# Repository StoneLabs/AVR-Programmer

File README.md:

# Stone Labs. AVR-Programmer
Schematics and firmware for a portable In-Service-Programmer. It is designed to be powered by a 9V battery and uses an OLED Display module for user interaction. INTEL HEX Files can be flashed to target chips via an ISP-6 port directly from an SD-Card.

# PCB

The Programmer is designed to sit on a portable ~9x11cm PCB. Eagle files for the PCB can be found in the `schematics` folder. Target chips can be programmed with the 6-pin Header located at the top of the PCB. There is also an 8Mhz clock pin available (TCLK) in case the target needs an external clock and none is available. BOM for the programmer can be found in `schematics/bom-grouped.csv`. All parts are available from DIGI-KEY. The price per assembled PCB should be around 10-30 bucks depending on the order quantity.

Aside from the programmer, there is target PCB design under `schematics-target`. The target can hold an ATmega328P like chip that can be programmed by connecting the target boards ISP Header to the programmer ISP-Port.

[Picture of PCB revision 1 (Release_V-1.0)](/pcb_v-1.0.png)

| PCB | Version | Status |
| - | - | - |
| Main PCB | Hardware_V-1.0 | Pull-Ups R1, R2 are connected incorrectly (to GND instead of +5V)! Assembled and tested. Works without R1, R2. |
| Main PCB | Hardware_V-1.1 | Fixed only R1, R2 and should work better than V-1.0. Untested! |
| Main PCB | Hardware_V-1.1+ | No functional hardware change. |
| Target PCB | Hardware_V-1.2 | Assembled and tested. Fully functional. |

# INTEL HEX

All `.hex` or `.HEX` files in the root folder of the SD-Card can be flashed to the target using the Programmer. The algorithm used for flashing the program to the target is very robust against weirdly formed hex files (e.g. line swaps, different lengths of lines in the same file, etc.). HEX record types 00, 01, and 02 are fully supported. Type 03 entries will be ignored with a warning sent to the programmers Serial output. Type 04 and 05 are not supported and HEX files containing those record types can't be flashed. (This shouldn't be an issue for AVR chips).

The programmer will also scan all possible bootloader positions for the current target and automatically set the fuse containing the bootloader position bits as needed.

# Supported chips

 Supported and tested  
 Supported not tested  
 Not yet supported  

||Chip||Chip|
| - | - | - | - |
|   | ATmega1280    |   | ATmega329A    |
|   | ATmega1281    |   | ATmega329PA   |
|   | ATmega1284P   |   | ATmega329P    |
|   | ATmega1284    |   | ATmega329     |
|   | ATmega128A    |   | ATmega32A     |
|   | ATmega128RFA1 |   | ATmega32C1    |
|   | ATmega128     |   | ATmega32HVB   |
|   | ATmega162     |   | ATmega32M1    |
|   | ATmega164A    |   | ATmega32U2    |
|   | ATmega164PA   |   | ATmega32U4    |
|   | ATmega164P    |   | ATmega32      |
|   | ATmega165A    |   | ATmega48A     |
|   | ATmega165PA   |   | ATmega48PA    |
|   | ATmega165P    |   | ATmega48P     |
|   | ATmega168A    |   | ATmega48      |
|   | ATmega168PA   |   | ATmega640     |
|   | ATmega168P    |   | ATmega644A    |
|   | ATmega168V    |   | ATmega644PA   |
|   | ATmega168     |   | ATmega644P    |
|   | ATmega169A    |   | ATmega644     |
|   | ATmega169PA   |   | ATmega6450A   |
|   | ATmega169P    |   | ATmega6450P   |
|   | ATmega16A     |   | ATmega6450    |
|   | ATmega16HVB   |   | ATmega645A    |
|   | ATmega16M1    |   | ATmega645P    |
|   | ATmega16U2    |   | ATmega645     |
|   | ATmega16U4    |   | ATmega6490A   |
|   | ATmega16      |   | ATmega6490P   |
|   | ATmega2560    |   | ATmega6490    |
|   | ATmega2561    |   | ATmega649A    |
|   | ATmega324A    |   | ATmega649P    |
|   | ATmega324PA   |   | ATmega649     |
|   | ATmega324P    |   | ATmega64A     |
|   | ATmega3250A   |   | ATmega64C1    |
|   | ATmega3250PA  |   | ATmega64M1    |
|   | ATmega3250P   |   | ATmega64      |
|   | ATmega3250    |   | ATmega8515    |
|   | ATmega325A    |   | ATmega8535    |
|   | ATmega325PA   |   | ATmega88A     |
|   | ATmega325P    |   | ATmega88PA    |
|   | ATmega325     |   | ATmega88P     |
|   | ATmega328P    |   | ATmega88      |
|   | ATmega328PB   |   | ATmega8A      |
|   | ATmega328     |   | ATmega8U2     |
|   | ATmega3290A   |   | ATmega8       |
|   | ATmega3290PA  |   | At90USB82     |
|   | ATmega3290P   |   | At90USB162    |
|   | ATmega3290    |                                                                  |               |
| | | | |
|   | ATtiny24      |   | ATtiny25      |
|   | ATtiny44      |   | ATtiny45      |
|   | ATtiny84      |   | ATtiny85      |

# License

This is free and unencumbered software released into the public domain.

Anyone is free to copy, modify, publish, use, compile, sell, or
distribute this software, either in source code form or as a compiled
binary, for any purpose, commercial or non-commercial, and by any
means.

In jurisdictions that recognize copyright laws, the author or authors
of this software dedicate any and all copyright interest in the
software to the public domain. We make this dedication for the benefit
of the public at large and to the detriment of our heirs and
successors. We intend this dedication to be an overt act of
relinquishment in perpetuity of all present and future rights to this
software under copyright law.

THE SOFTWARE IS PROVIDED "AS IS", WITHOUT WARRANTY OF ANY KIND,
EXPRESS OR IMPLIED, INCLUDING BUT NOT LIMITED TO THE WARRANTIES OF
MERCHANTABILITY, FITNESS FOR A PARTICULAR PURPOSE AND NONINFRINGEMENT.
IN NO EVENT SHALL THE AUTHORS BE LIABLE FOR ANY CLAIM, DAMAGES OR
OTHER LIABILITY, WHETHER IN AN ACTION OF CONTRACT, TORT OR OTHERWISE,
ARISING FROM, OUT OF OR IN CONNECTION WITH THE SOFTWARE OR THE USE OR
OTHER DEALINGS IN THE SOFTWARE.

For more information, please refer to <http://unlicense.org/>

### That being said, I'd really like to hear from you if you plan on using this project somewhere. And I for sure wouldn't mind some part if you use it commercially ;) (e.g. selling it etc.)

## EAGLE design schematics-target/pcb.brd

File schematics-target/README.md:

# Schematics

Eagle files for a simple target board holding an ATmega328P like chip in PDIP packaging. It can be used to easily hook up target chips.

The Graphics on the pcb can be found in media/.

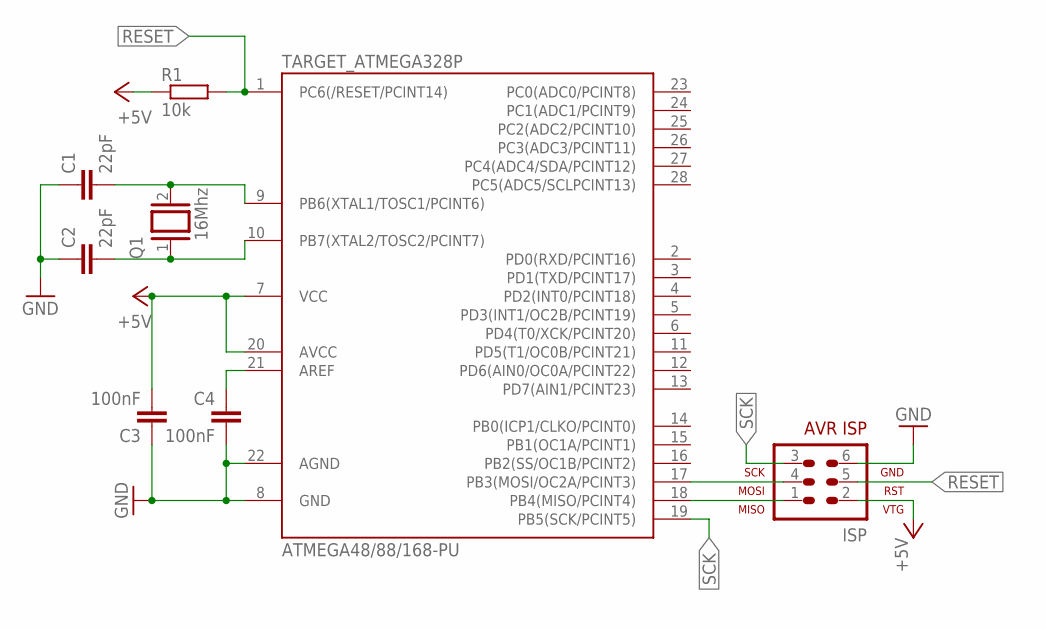
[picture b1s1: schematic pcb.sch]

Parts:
C1, C2: 22pF; C0805
C3, C4: 100nF; C0805
ISP: AVR-ISP-6
Q1: 16Mhz; QS
R1: 10k; R0805
TARGET_ATMEGA328P: ATMEGA48/88/168-PU; DIL28-3

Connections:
+5V: C3.2, ISP.2, R1.1, TARGET_ATMEGA328P.7 (VCC), TARGET_ATMEGA328P.20 (AVCC)
GND: C1.1, C2.1, C3.1, C4.2, ISP.6, TARGET_ATMEGA328P.8 (GND), TARGET_ATMEGA328P.22 (AGND)
unnamed: ISP.4, TARGET_ATMEGA328P.17 (PB3(MOSI/OC2A/PCINT3))
unnamed: ISP.1, TARGET_ATMEGA328P.18 (PB4(MISO/PCINT4))
unnamed: C1.2, Q1.2, TARGET_ATMEGA328P.9 (PB6(XTAL1/TOSC1/PCINT6))
unnamed: C2.2, Q1.1, TARGET_ATMEGA328P.10 (PB7(XTAL2/TOSC2/PCINT7))
unnamed: C4.1, TARGET_ATMEGA328P.21 (AREF)
RESET: ISP.5, R1.2, TARGET_ATMEGA328P.1 (PC6(/RESET/PCINT14))
SCK: ISP.3, TARGET_ATMEGA328P.19 (PB5(SCK/PCINT5))

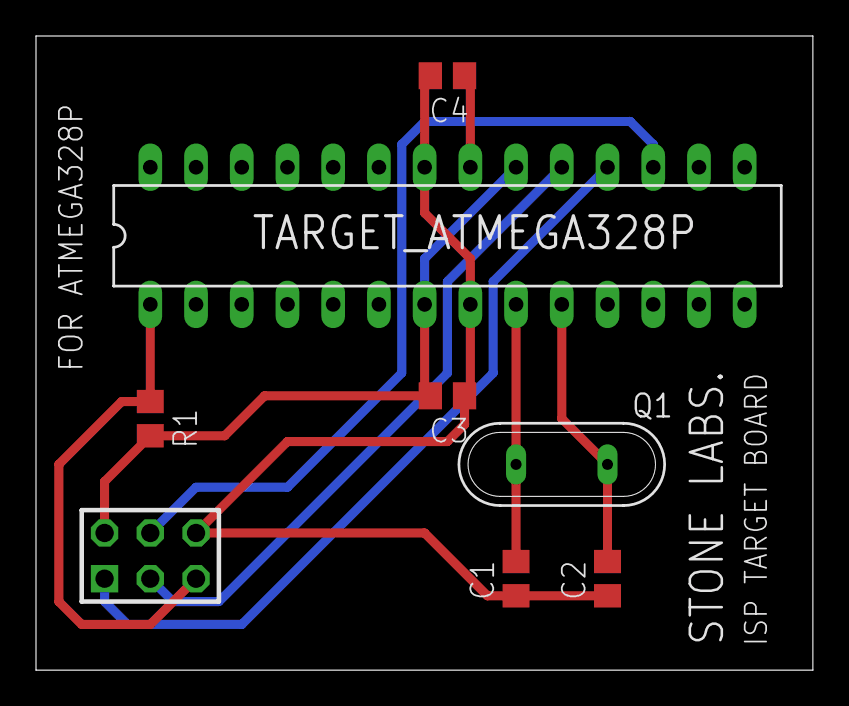
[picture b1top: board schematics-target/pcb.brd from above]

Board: 2 copper layers, 43.2 x 35.2 mm, 8 parts (0 on the bottom side), 9 nets.

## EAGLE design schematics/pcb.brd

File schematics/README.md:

# Schematics

Eagle files for the programmer board as well as a diagram for arduino based testing (arduino_wiring.sch).

Parts.lbr contains the OLED screen used. (see also oled.jpg)

The Graphics on the pcb can be found in media/.

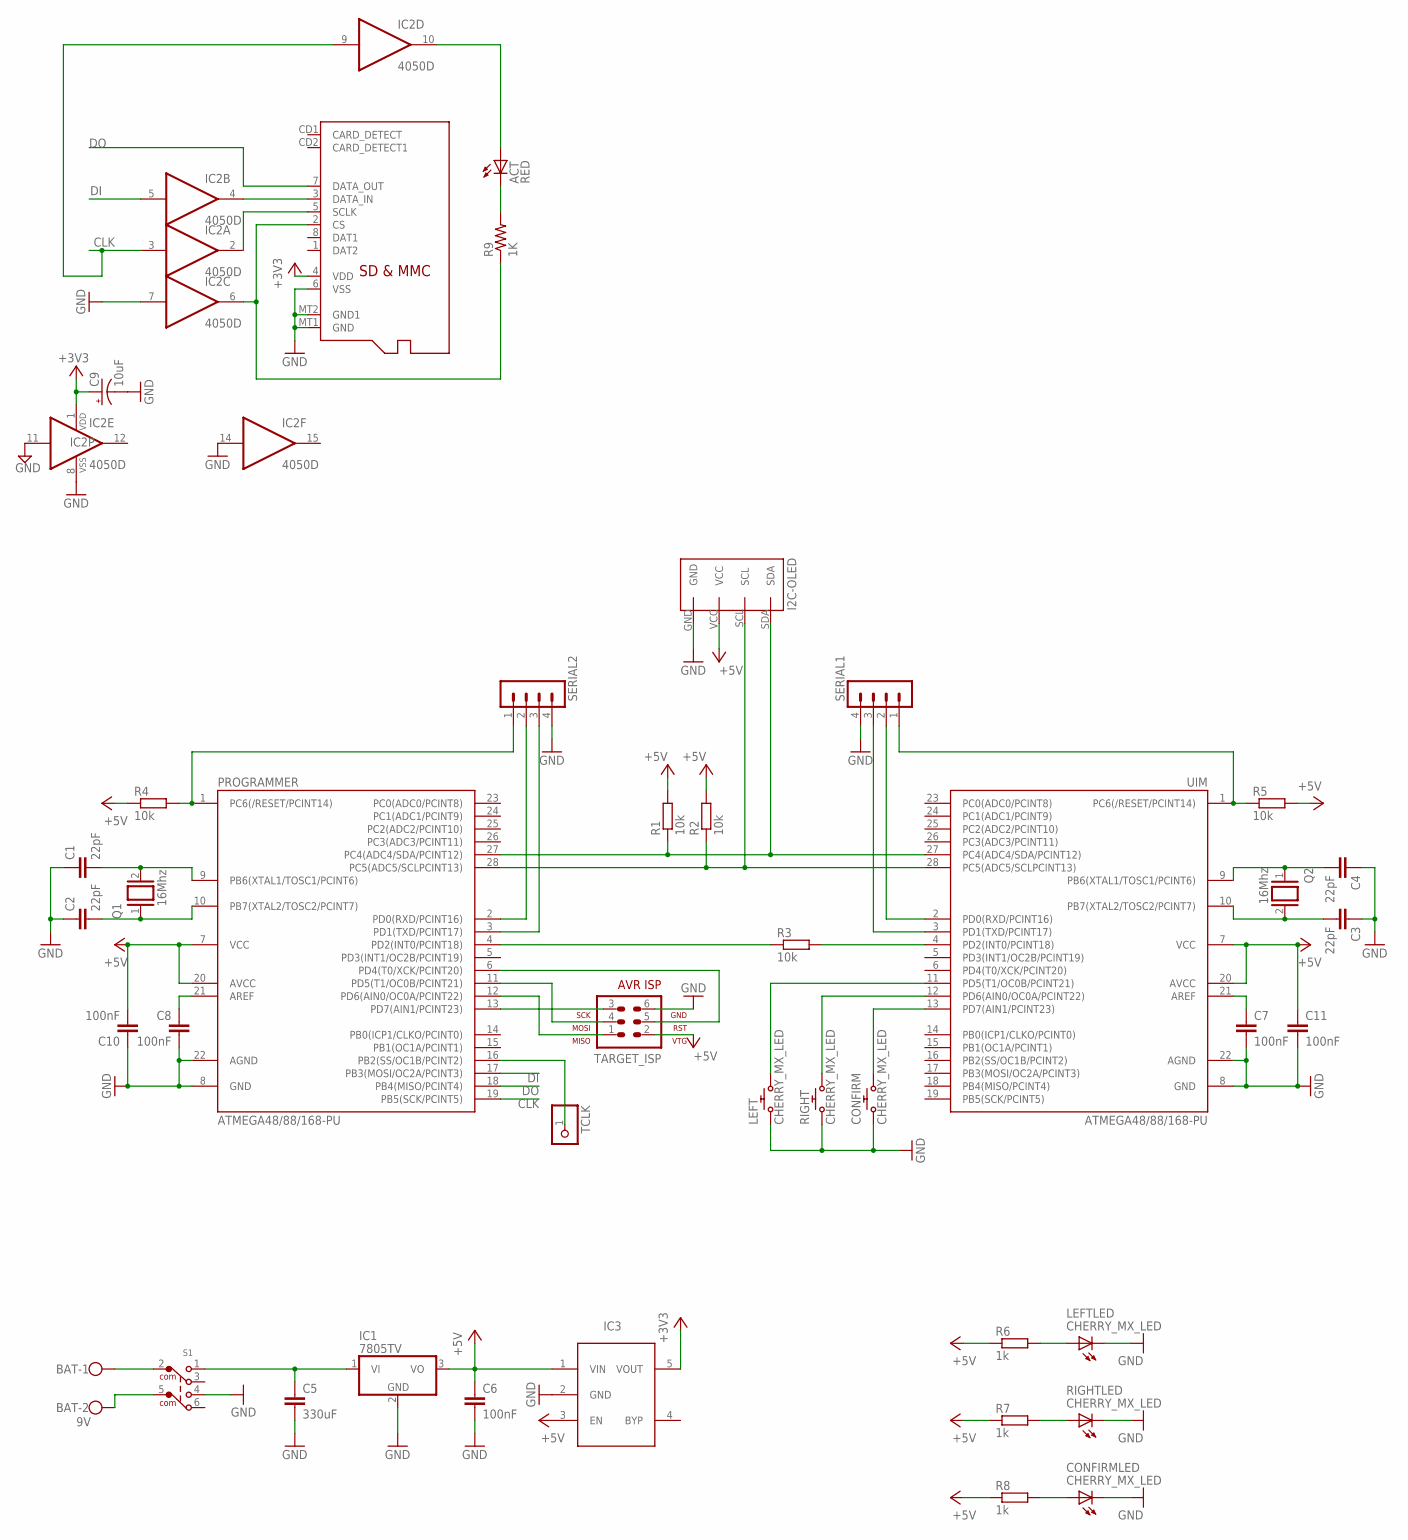
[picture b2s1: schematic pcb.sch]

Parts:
ACT: RED; CHIP-LED0805
BAT: 9V; W237-102
C1, C2, C3, C4: 22pF; C0805
C5: 330uF; C0805
C6, C7, C8, C10, C11: 100nF; C0805
C9: 10uF; A/3216-18R
CONFIRM: CHERRY_MX_LED
IC1: 7805TV; TO220V
IC2: 4050D; SO16
IC3: LP298XS; SOT23-5L
LEFT: CHERRY_MX_LED
PROGRAMMER: ATMEGA48/88/168-PU; DIL28-3
Q1, Q2: 16Mhz; QS
R1, R2, R3, R4, R5: 10k; R0805
R6, R7, R8: 1k; R0805
R9: 1K; R0805
RIGHT: CHERRY_MX_LED
S1: 452404020202
SERIAL1, SERIAL2: MA04-1
TARGET_ISP: AVR-ISP-6
TCLK: PINHD-1X1; 1X01
U$1: 128X64-I2C-OLED
UIM: ATMEGA48/88/168-PU; DIL28-3
X1: MICROSD

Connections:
9V+: C5.1, IC1.1 (VI), S1.1
+3V3: C9.+, IC2.1 (VDD), IC3.5 (VOUT), X1.4 (VDD)
+5V: C6.1, C10.2, C11.1, IC1.3 (VO), IC3.1 (VIN), IC3.3 (EN), PROGRAMMER.7 (VCC), PROGRAMMER.20 (AVCC), R1.2, R2.2, R4.1, R5.2, R6.1, R7.1, R8.1, TARGET_ISP.2, U$1.VCC, UIM.7 (VCC), UIM.20 (AVCC)
B$1: PROGRAMMER.11 (PD5(T1/OC0B/PCINT21)), TARGET_ISP.4
BAT+: BAT.1, S1.2 (COM)
BAT-: BAT.2, S1.5 (COM1)
CLK: IC2.3 (I), IC2.9 (I), PROGRAMMER.19 (PB5(SCK/PCINT5))
DI: IC2.5 (I), PROGRAMMER.17 (PB3(MOSI/OC2A/PCINT3))
DO: PROGRAMMER.18 (PB4(MISO/PCINT4)), X1.7 (DATA_OUT)
GND: C1.1, C2.1, C3.1, C4.1, C5.2, C6.2, C7.2, C8.2, C9.-, C10.1, C11.2, CONFIRM.L2 (C), CONFIRM.S1 (1), IC1.2 (GND), IC2.7 (I), IC2.8 (VSS), IC2.11 (I), IC2.14 (I), IC3.2 (GND), LEFT.L2 (C), LEFT.S1 (1), PROGRAMMER.8 (GND), PROGRAMMER.22 (AGND), RIGHT.L2 (C), RIGHT.S1 (1), S1.4, SERIAL1.4, SERIAL2.4, TARGET_ISP.6, U$1.GND, UIM.8 (GND), UIM.22 (AGND), X1.6 (VSS), X1.MT1 (GND), X1.MT2 (GND1)
unnamed: PROGRAMMER.28 (PC5(ADC5/SCLPCINT13)), R2.1, U$1.SCL, UIM.28 (PC5(ADC5/SCLPCINT13))
unnamed: PROGRAMMER.27 (PC4(ADC4/SDA/PCINT12)), R1.1, U$1.SDA, UIM.27 (PC4(ADC4/SDA/PCINT12))
unnamed: PROGRAMMER.4 (PD2(INT0/PCINT18)), R3.1
unnamed: R3.2, UIM.4 (PD2(INT0/PCINT18))
unnamed: PROGRAMMER.1 (PC6(/RESET/PCINT14)), R4.2, SERIAL2.1
unnamed: R5.1, SERIAL1.1, UIM.1 (PC6(/RESET/PCINT14))
unnamed: C1.2, PROGRAMMER.9 (PB6(XTAL1/TOSC1/PCINT6)), Q1.2
unnamed: C2.2, PROGRAMMER.10 (PB7(XTAL2/TOSC2/PCINT7)), Q1.1
unnamed: LEFT.S2 (2), UIM.11 (PD5(T1/OC0B/PCINT21))
unnamed: C3.2, Q2.2, UIM.10 (PB7(XTAL2/TOSC2/PCINT7))
unnamed: C4.2, Q2.1, UIM.9 (PB6(XTAL1/TOSC1/PCINT6))
unnamed: PROGRAMMER.12 (PD6(AIN0/OC0A/PCINT22)), TARGET_ISP.1
unnamed: PROGRAMMER.13 (PD7(AIN1/PCINT23)), TARGET_ISP.3
unnamed: PROGRAMMER.6 (PD4(T0/XCK/PCINT20)), TARGET_ISP.5
unnamed: RIGHT.S2 (2), UIM.12 (PD6(AIN0/OC0A/PCINT22))
unnamed: CONFIRM.S2 (2), UIM.13 (PD7(AIN1/PCINT23))
unnamed: LEFT.L1 (A), R6.2
unnamed: R7.2, RIGHT.L1 (A)
unnamed: CONFIRM.L1 (A), R8.2
unnamed: C7.1, UIM.21 (AREF)
unnamed: C8.1, PROGRAMMER.21 (AREF)
unnamed: ACT.A, IC2.10 (O)
unnamed: IC2.2 (O), X1.5 (SCLK)
unnamed: IC2.6 (O), R9.1, X1.2 (CS)
unnamed: ACT.C, R9.2
unnamed: IC2.4 (O), X1.3 (DATA_IN)
unnamed: PROGRAMMER.16 (PB2(SS/OC1B/PCINT2)), TCLK.1
unnamed: PROGRAMMER.2 (PD0(RXD/PCINT16)), SERIAL2.2
unnamed: PROGRAMMER.3 (PD1(TXD/PCINT17)), SERIAL2.3
unnamed: SERIAL1.2, UIM.2 (PD0(RXD/PCINT16))
unnamed: SERIAL1.3, UIM.3 (PD1(TXD/PCINT17))

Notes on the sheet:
I2C-OLED

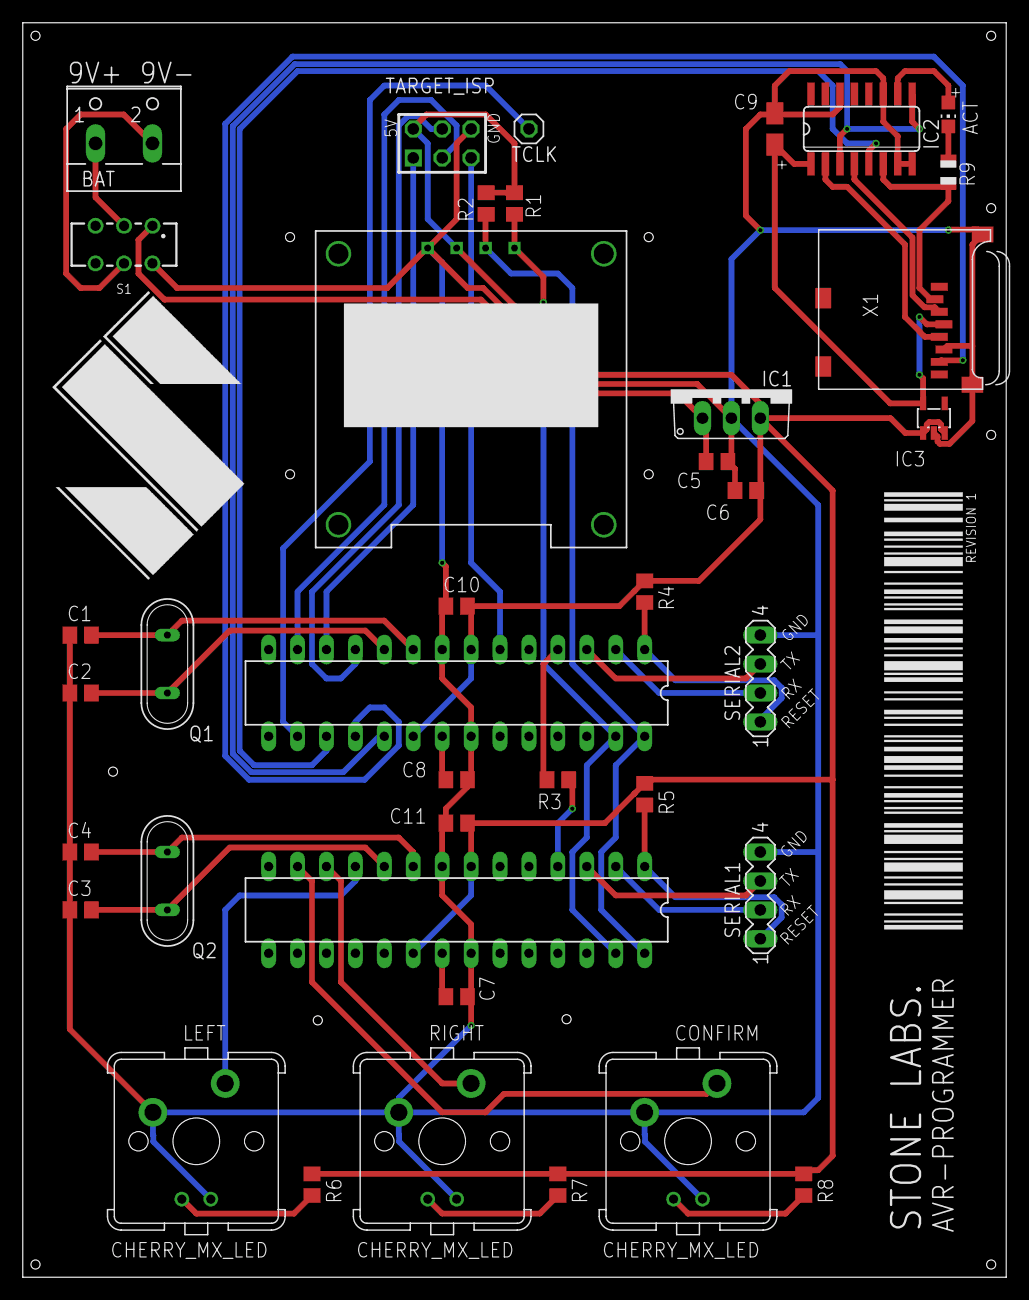
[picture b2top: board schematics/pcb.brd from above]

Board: 2 copper layers, 86.4 x 110.2 mm, 39 parts (0 on the bottom side), 41 nets.

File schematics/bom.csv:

Part,Value,Device,Package,Description
ACT,RED,LEDCHIP-LED0805,CHIP-LED0805,LED
BAT,9V,W237-102,W237-102,WAGO SCREW CLAMP
C1,22pF,C-EUC0805,C0805,"CAPACITOR, European symbol"
C2,22pF,C-EUC0805,C0805,"CAPACITOR, European symbol"
C3,22pF,C-EUC0805,C0805,"CAPACITOR, European symbol"
C4,22pF,C-EUC0805,C0805,"CAPACITOR, European symbol"
C5,330uF,C-EUC0805,C0805,"CAPACITOR, European symbol"
C6,100nF,C-EUC0805,C0805,"CAPACITOR, European symbol"
C7,100nF,C-EUC0805,C0805,"CAPACITOR, European symbol"
C8,100nF,C-EUC0805,C0805,"CAPACITOR, European symbol"
C9,10uF,CPOL-USA/3216-18R,A/3216-18R,"POLARIZED CAPACITOR, American symbol"
C10,100nF,C-EUC0805,C0805,"CAPACITOR, European symbol"
C11,100nF,C-EUC0805,C0805,"CAPACITOR, European symbol"
CONFIRM,CHERRY_MX_LED,CHERRY_MX_LED,CHERRY_MX_LED,Cherry MX with LED
IC1,7805TV,7805TV,TO220V,Positive VOLTAGE REGULATOR
IC2,4050D,4050D,SO16,Hex non-inverting BUFFER
IC3,LP298XS,LP298XS,SOT23-5L,
LEFT,CHERRY_MX_LED,CHERRY_MX_LED,CHERRY_MX_LED,Cherry MX with LED
PROGRAMMER,ATMEGA48/88/168-PU,ATMEGA48/88/168-PU,DIL28-3,
Q1,16Mhz,XTAL/S,QS,CRYSTAL
Q2,16Mhz,XTAL/S,QS,CRYSTAL
R1,10k,R-EU_R0805,R0805,"RESISTOR, European symbol"
R2,10k,R-EU_R0805,R0805,"RESISTOR, European symbol"
R3,10k,R-EU_R0805,R0805,"RESISTOR, European symbol"
R4,10k,R-EU_R0805,R0805,"RESISTOR, European symbol"
R5,10k,R-EU_R0805,R0805,"RESISTOR, European symbol"
R6,1k,R-EU_R0805,R0805,"RESISTOR, European symbol"
R7,1k,R-EU_R0805,R0805,"RESISTOR, European symbol"
R8,1k,R-EU_R0805,R0805,"RESISTOR, European symbol"
R9,1K,R-US_R0805,R0805,"RESISTOR, American symbol"
RIGHT,CHERRY_MX_LED,CHERRY_MX_LED,CHERRY_MX_LED,Cherry MX with LED
S1, ,452404020202,452404020202,"WS-SLTV THT Mini Slide Switch, Same Side Connection 9.0x3.5 mm"
SERIAL1,,MA04-1,MA04-1,PIN HEADER
SERIAL2,,MA04-1,MA04-1,PIN HEADER
TARGET_ISP,AVR-ISP-6,AVR-ISP-6,AVR-ISP-6,AVR ISP-6 Serial Programming Header
TCLK,,PINHD-1X1,1X01,PIN HEADER
U$1,128X64-I2C-OLED,128X64-I2C-OLED,128X64-I2C-OLED,
UIM,ATMEGA48/88/168-PU,ATMEGA48/88/168-PU,DIL28-3,
X1,MICROSD,MICROSD,MICROSD,Micro-SD / Transflash card holder with SPI pinout

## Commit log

2020-03-17 Added signature reading to BBProgrammer
2020-03-18 Added chip erase functionality.
2020-03-18 Optimized code base
2020-03-18 Implemented Fuse reading; Fixed clock (now on OC1B)
2020-03-18 Renamed minor opcodes; Changes to signature list
2020-03-18 Implemented SD-Card file listing; Removed image as replaced by SD-Card
2020-03-19 Implemented line by line file reading
2020-03-19 Memory usage optimization
2020-03-19 Implemented hex processing and page creation; Changed baud rate
2020-03-19 Implemented Intel HEX 'Extended Segment Address' record (untested)
2020-03-19 Implemented page buffer flashing with BBProgrammer;
2020-03-19 Implemented bootloader detection
2020-03-19 Implemented high and low fuse writing; Mulitple minor bugfixes
2020-03-20 Overhaul of debug system.
2020-03-20 Restructued repo folders
2020-03-20 Added references
2020-03-20 Added user interface module project with sample sketch
2020-03-21 Changed OLED library; Main menu sketch
2020-03-21 Implemented PageManager; Implemented cosmetical delay Page;
2020-03-22 Menu partial rendering optimization
2020-03-22 Implemented Programmer UIM communication with fake-programmer;
2020-03-22 Added abstraction layer for loading pages;
2020-03-22 Implemented InitPage which check for programmer response instead of fixed time
2020-03-22 Implemented fake signature in fake_programmer
2020-03-22 Fnished signature page;
2020-03-23 Implemented chip erase page;
2020-03-23 Implemented current UIM functionality in firmware_programmer; Minor fixes in BBProgrammer
2020-03-23 Implemented fuse reading page
2020-03-23 Fixed buffer overflow and memory leak in Signature page;
2020-03-23 Implemented file selection with functionality
2020-03-23 Implemented boot page waiting for programmer to become available
2020-03-24 Implemented Flashing of file with functionality (currently constant file) in UIM
2020-03-24 Removed main Init Page as it is not really needed; Fixed multiple memory "violation" issues where page members would be used after being deleted; Minor optimizations, changes, fixes
2020-03-24 Implemented command arguments of 31 bytes;
2020-03-24 Finished flashFilePage implementation
2020-03-24 Fixed programmer debug output on command 0x11
2020-03-24 Implemented Programmer error handling functionality in UIM
2020-03-24 Added numerous error checks
2020-03-24 Moved all display String from RAM to Flash
2020-03-24 Implemented write Fuse selection Page.
2020-03-24 Implemented Fuse writing page without functionality in programmer
2020-03-24 Fixed left button behaviour in tabPages
2020-03-24 Fully implemented fuse changing with full error handling
2020-03-24 Fixed bugs in firmware-programmer
2020-03-24 Release version v-1.0
2020-03-25 Added Arduino based wiring schematics
2020-03-26 Fixed mistakes in arduino based schematics
2020-03-28 Started work on PCB schematics
2020-03-28 Further work on pcb schematics
2020-03-29 Added SD-Card to PCB
2020-03-29 Added Serial debug and reprogramming port to ICs
2020-03-29 Added PCB Board with placed components (WIP)
2020-03-30 Updated OLED module in part library; Scraped current PCB placements
2020-03-30 Further updates to OLED module
2020-04-03 PCB part placements and partial routing
2020-04-03 Finished PCB routing
2020-04-03 PCB text cleanup
2020-04-03 Added OLED dimension sketch to schematics
2020-04-04 Added media files
2020-04-04 PLaced images on PCB
2020-04-04 Added PCB mounting holes
2020-04-04 Added BOM files
2020-04-14 Fixed I2C Pull-ups being Pull-downs
2020-04-14 Minor code optimizations
2020-04-14 Added Revision 1 indicator to PCB
2020-04-14 Added readme
2020-05-06 Moved PCB Text away from SMD pads
2020-05-06 Added PCB (1.0) image to readme
2020-05-06 Fixed Readme image
2020-05-15 Added readme files in subdirectories
2020-05-15 Added schematics for target board
2020-05-15 Added target PCB board file
2020-05-15 Further work on target board
2020-05-15 Added support table to readme
2020-05-15 Added support for numerous chips
2020-05-15 Added transperent StoneLabs logo to schematics media
2020-05-15 Readme cleanup, shields
2020-05-16 Added support for ATmega2560 and ATmega2561 chips
2020-05-18 Added support for chips without bootloader capability
2020-05-18 Added support for chips with bootloader bits in extFuse
2020-05-18 Updated readme with new version naming scheme
2020-05-18 Added current chip name/signature to fuse input page
2020-05-18 Added name of currently selected fuse bit to fuse input page
2020-05-18 Fixed project file not including some files
2020-05-19 Added flowchart for UI interaction
2020-05-19 Added UI flowchart to UIM readme
2020-05-19 Added informative text to pins on main pcb
2020-05-27 Updated readme hardware table
2020-05-27 Added more description to readme
2020-05-28 Updated part names in target PCB
2020-05-28 Added BOM for target PCB

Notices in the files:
parts and their libraries:
Wurth_Switch_WS-SLTV: Copyright: Würth Elektronik
